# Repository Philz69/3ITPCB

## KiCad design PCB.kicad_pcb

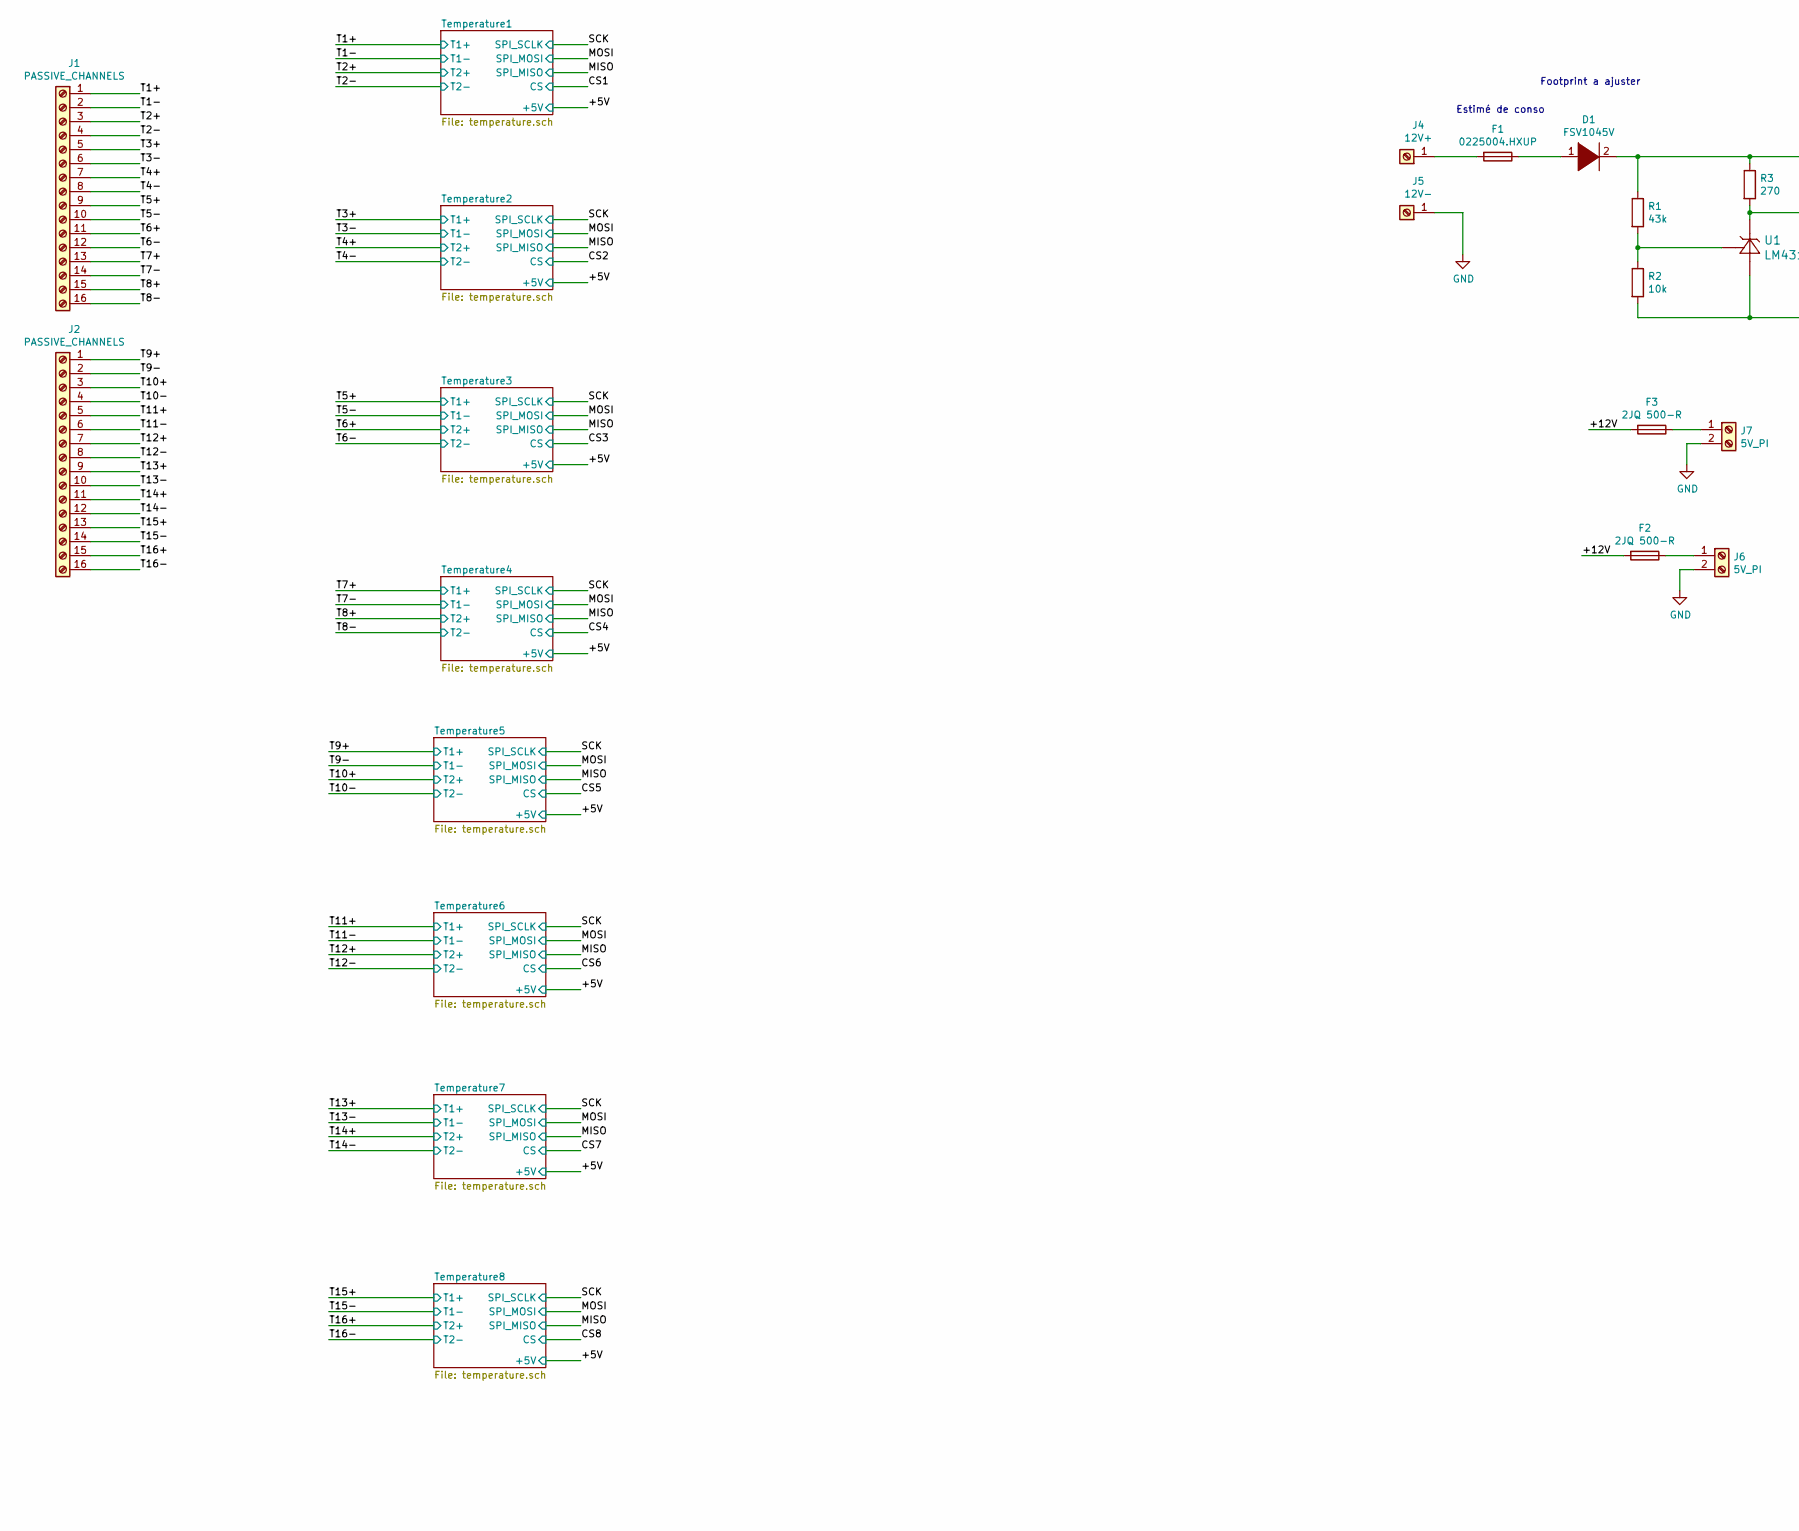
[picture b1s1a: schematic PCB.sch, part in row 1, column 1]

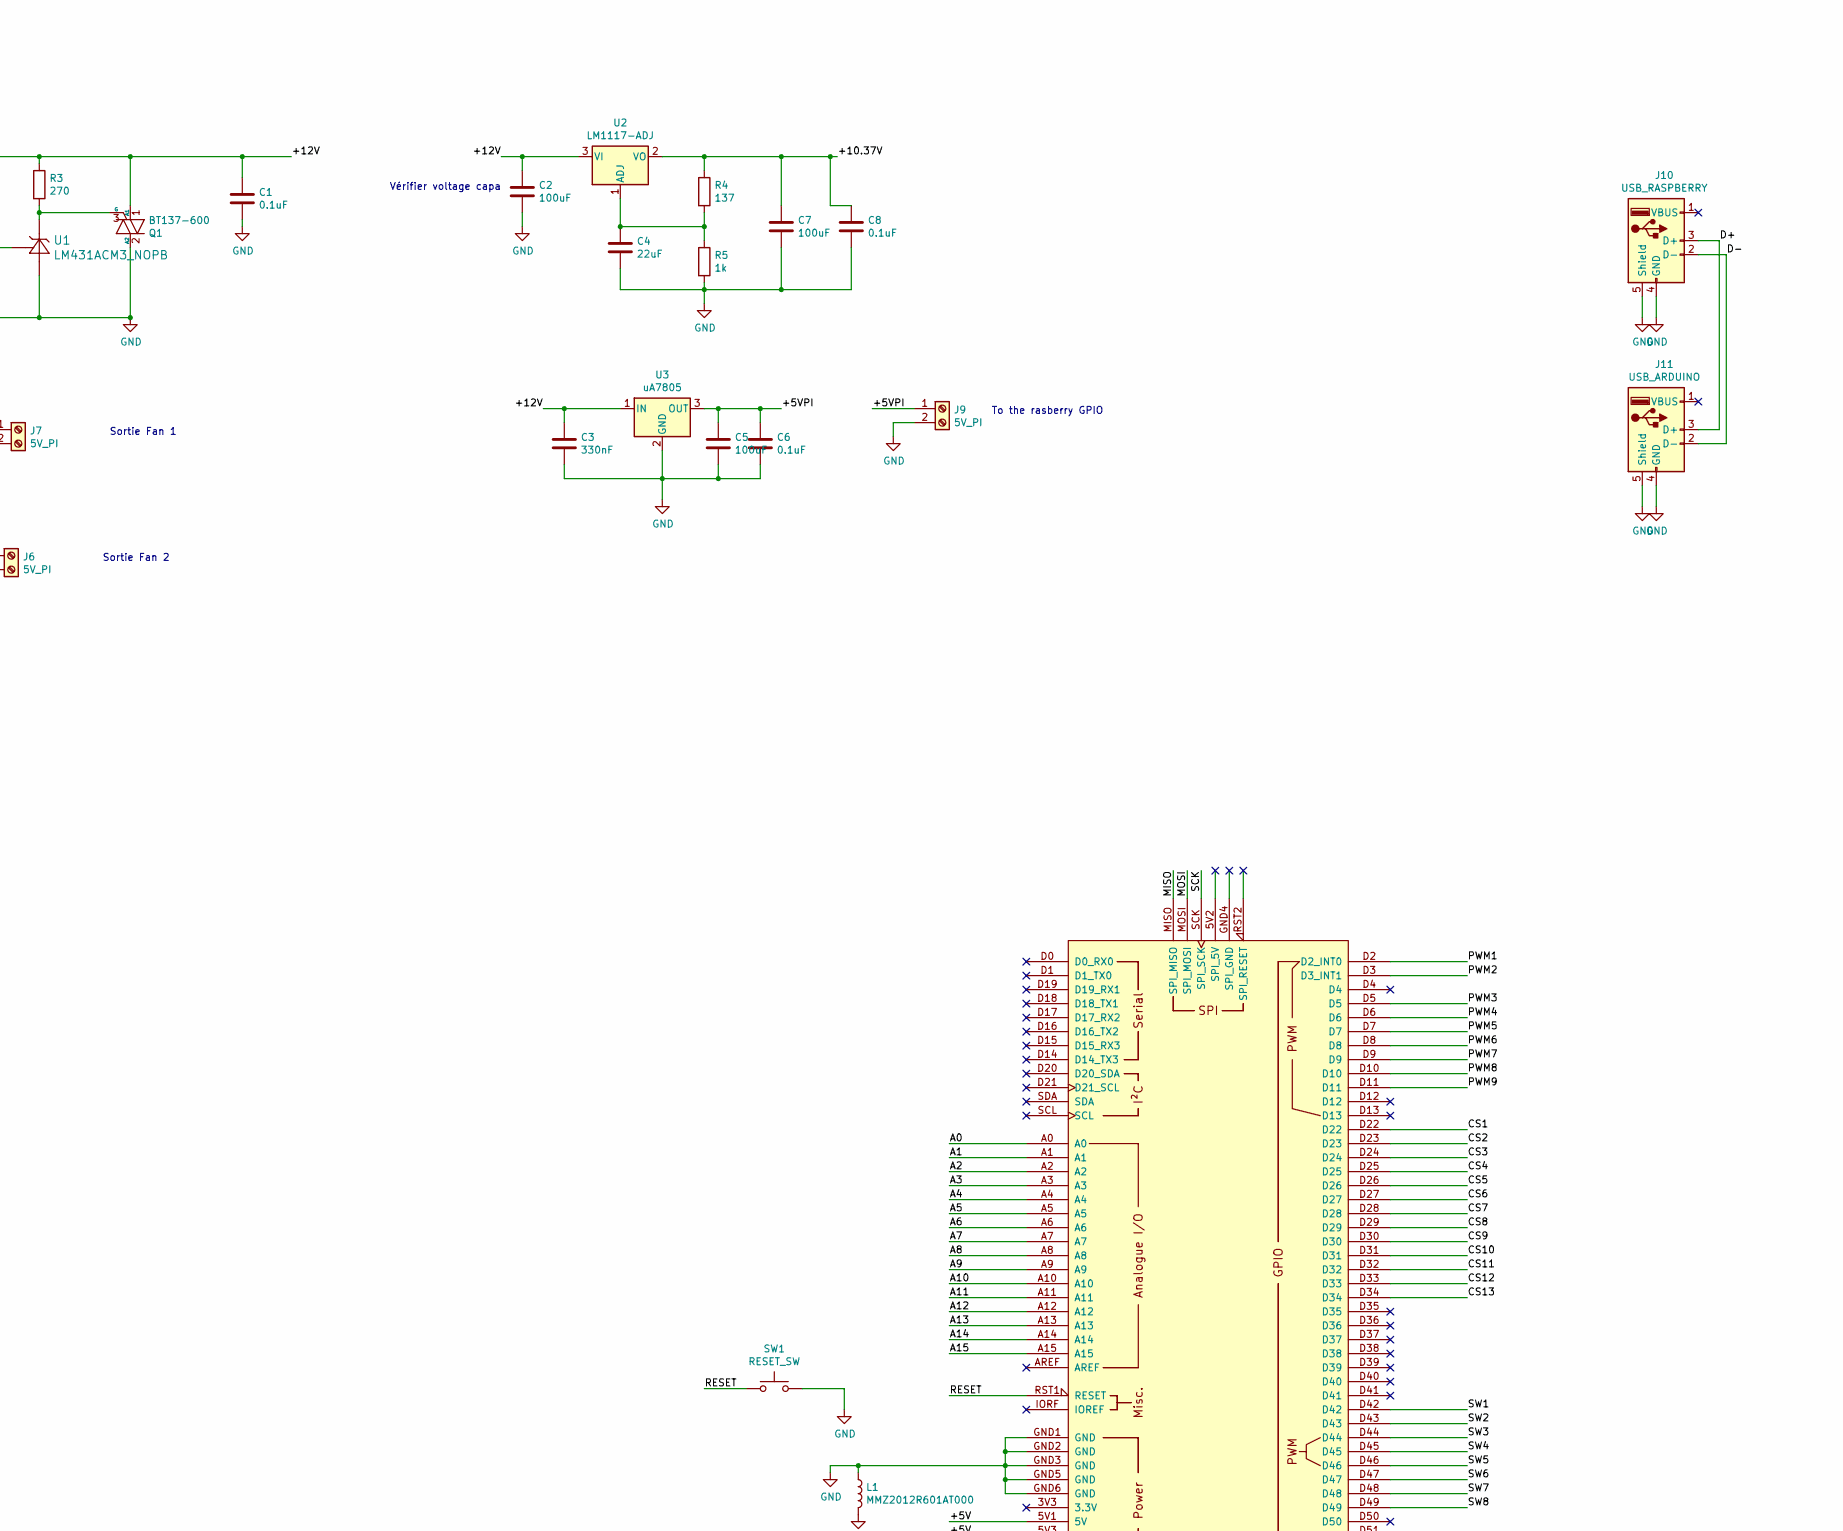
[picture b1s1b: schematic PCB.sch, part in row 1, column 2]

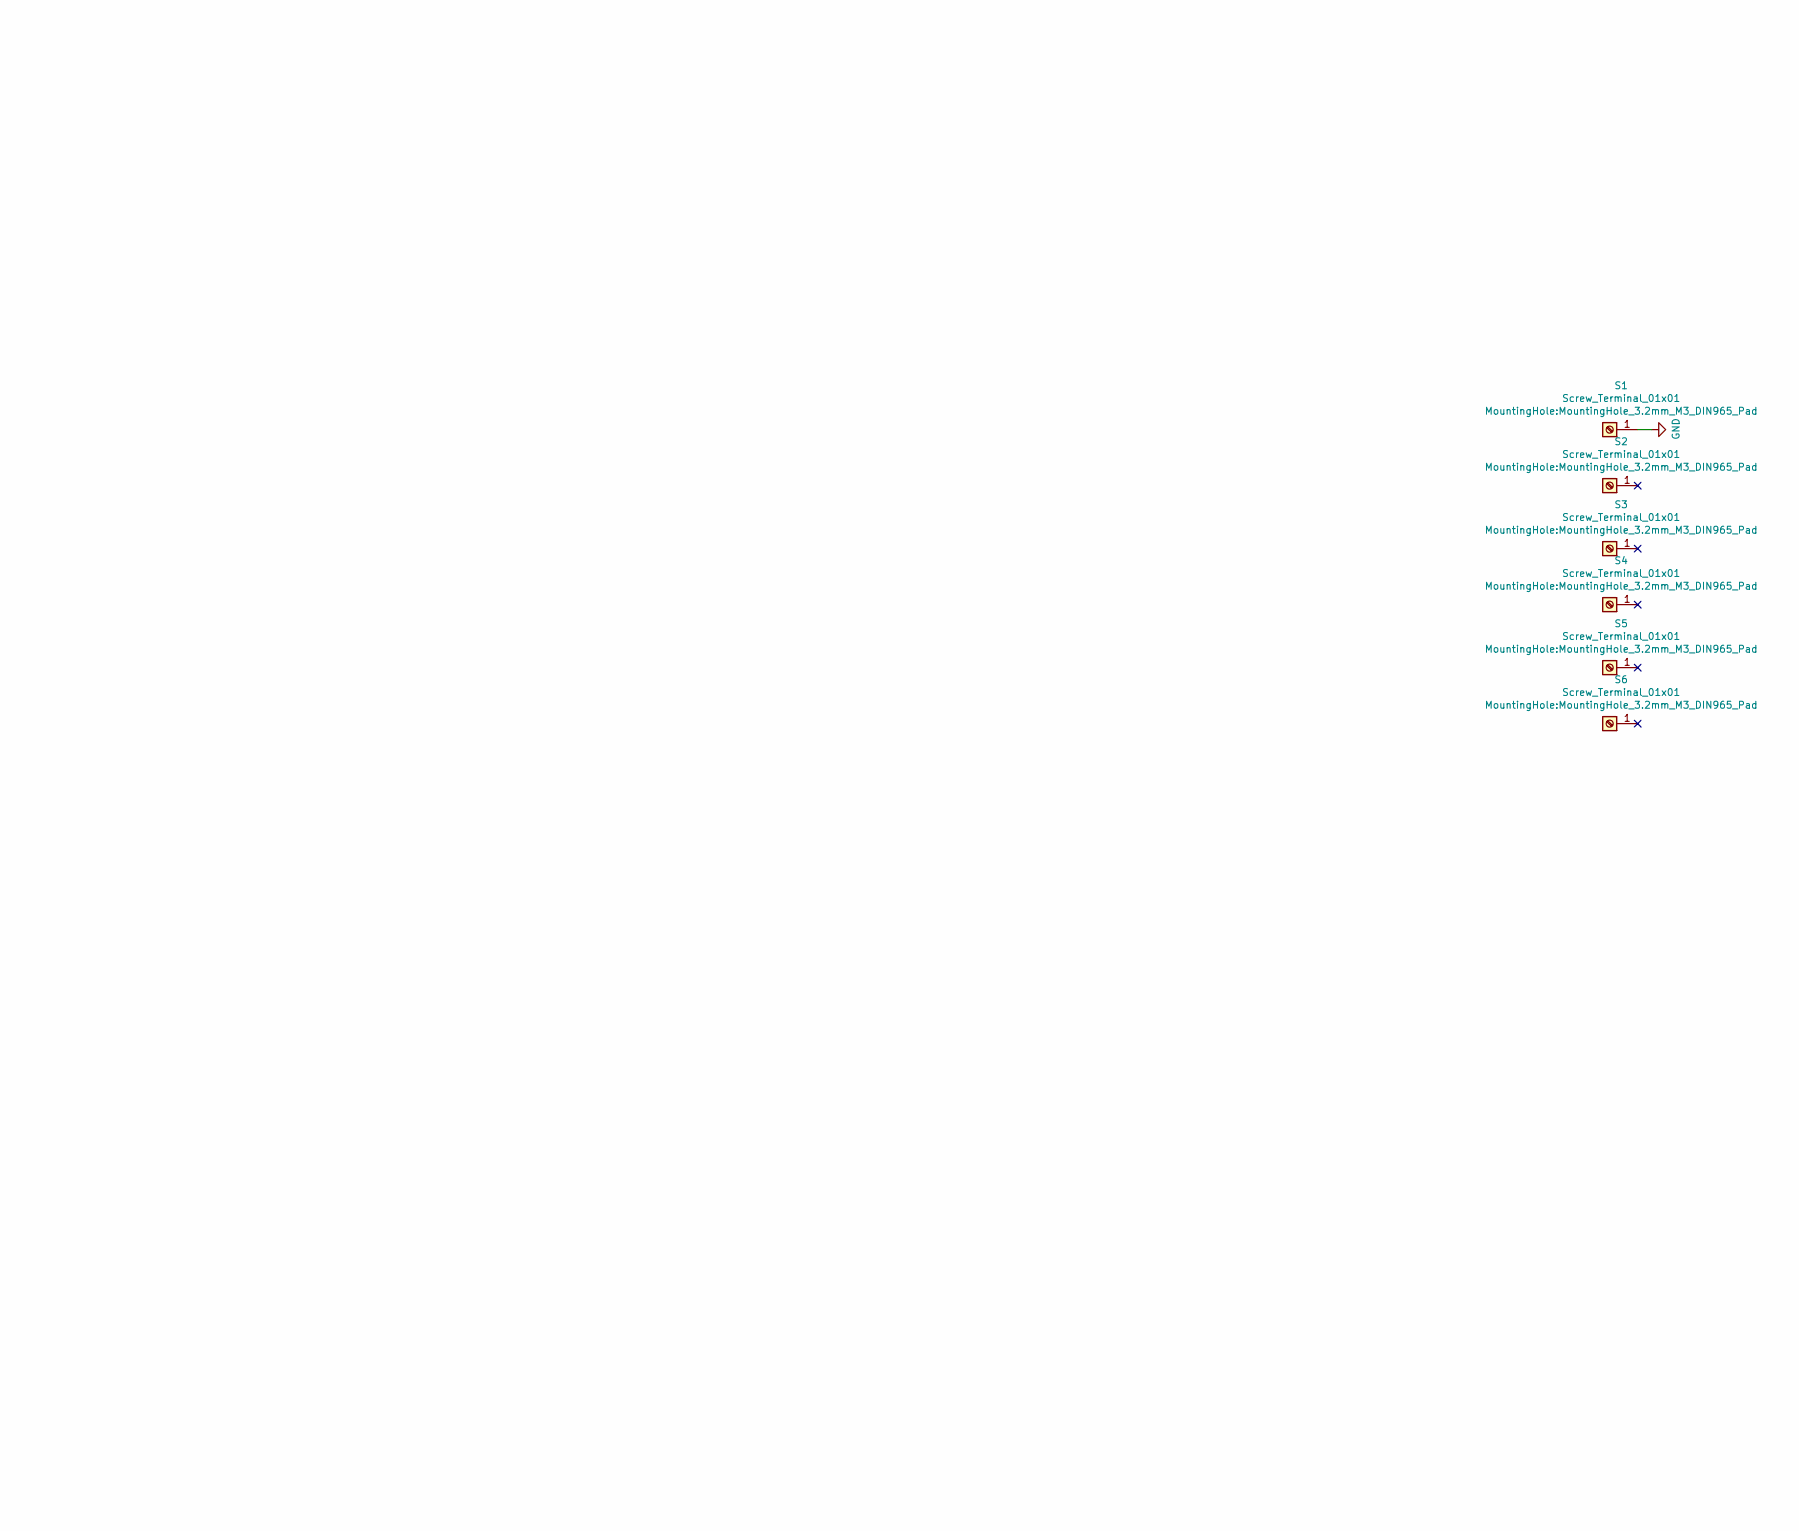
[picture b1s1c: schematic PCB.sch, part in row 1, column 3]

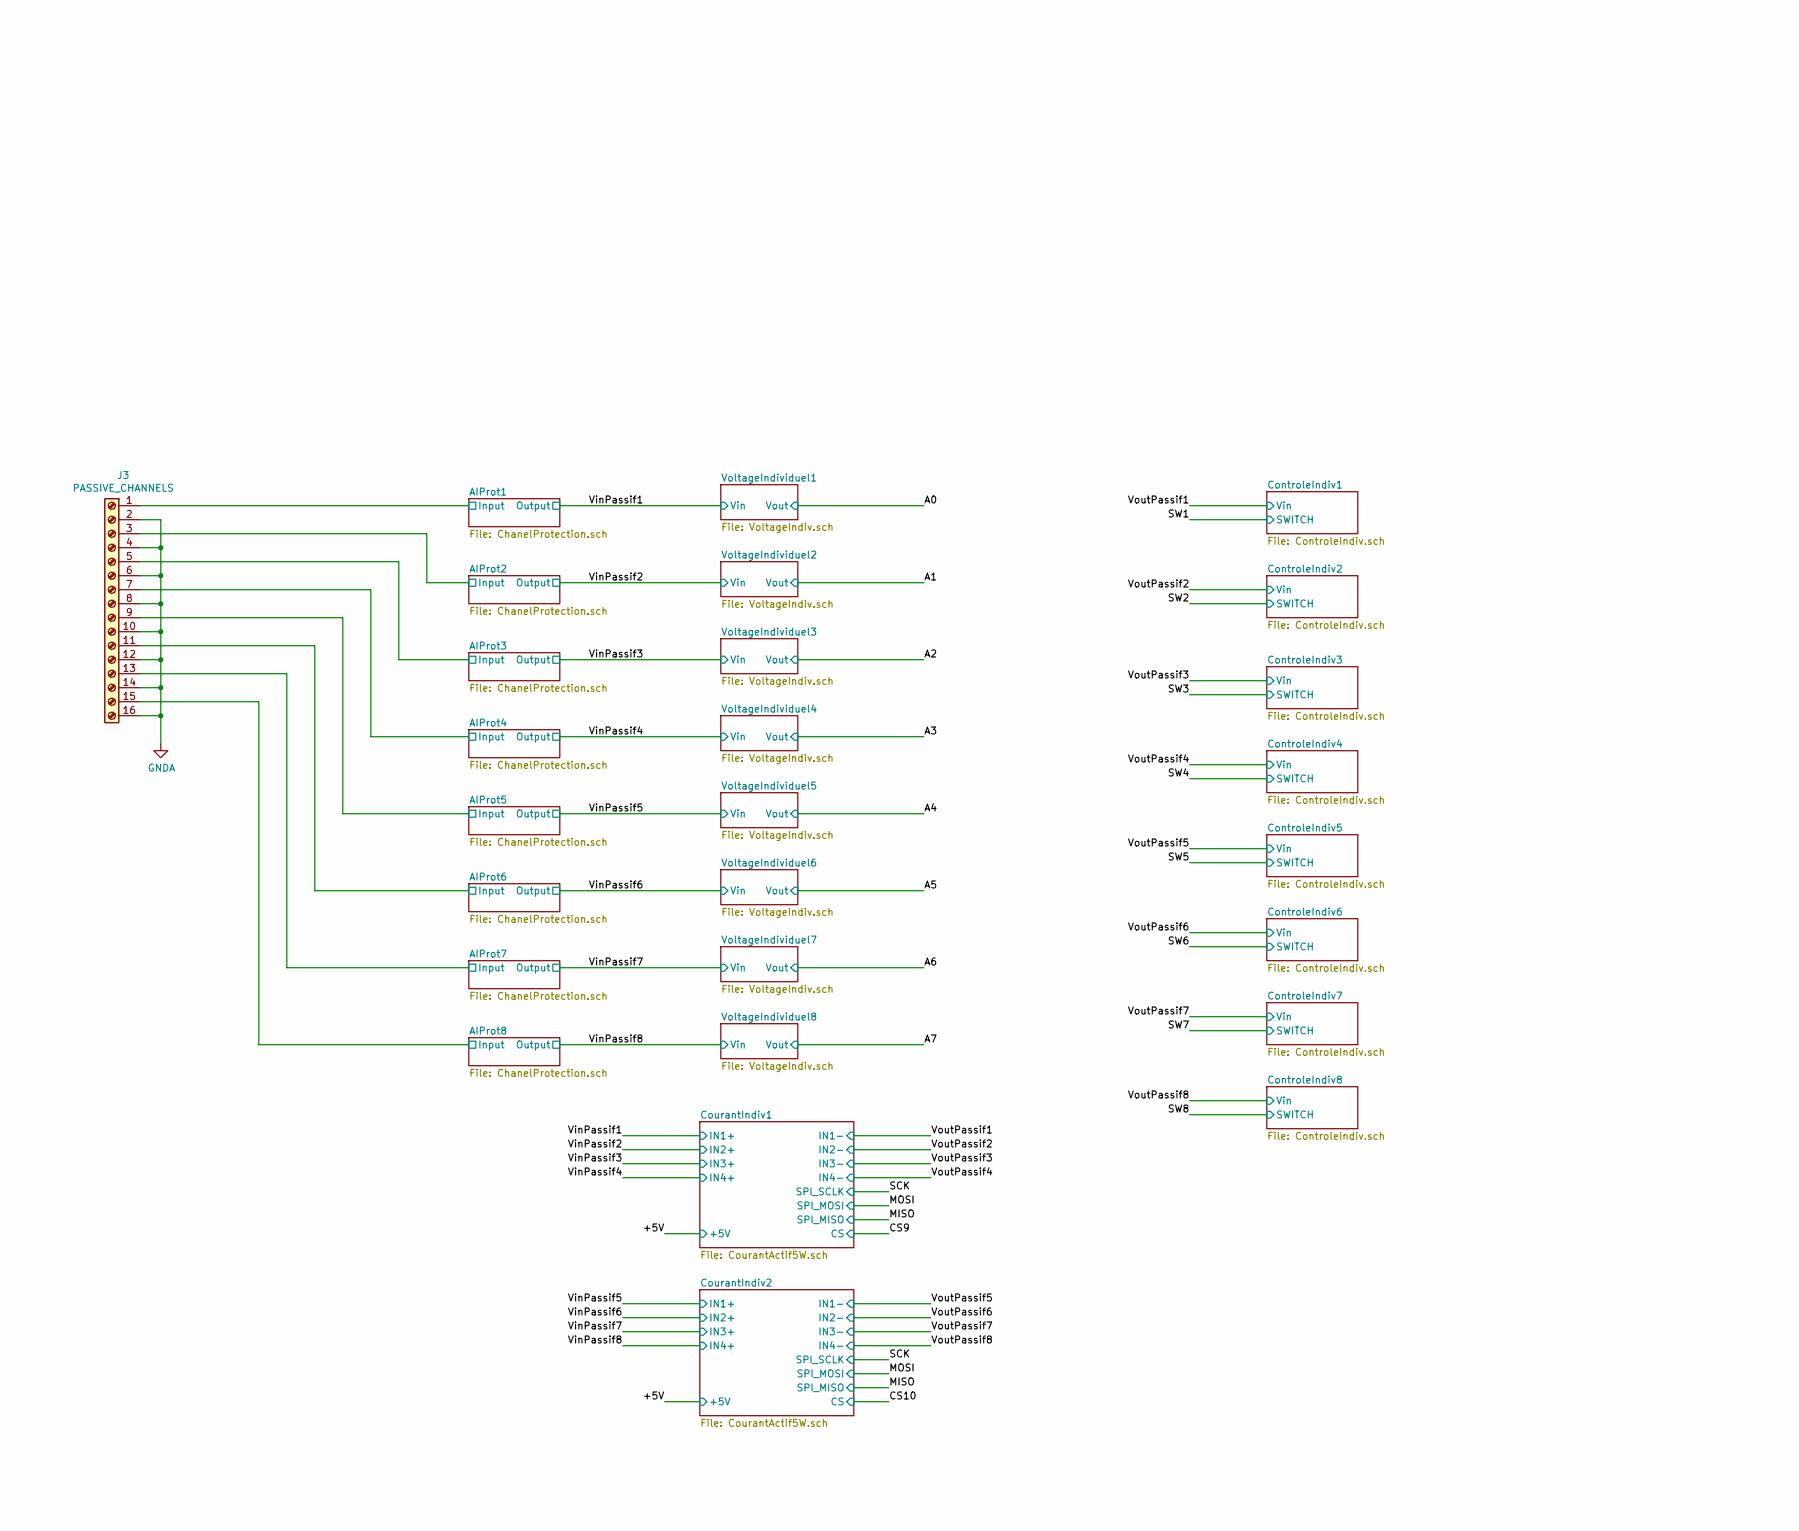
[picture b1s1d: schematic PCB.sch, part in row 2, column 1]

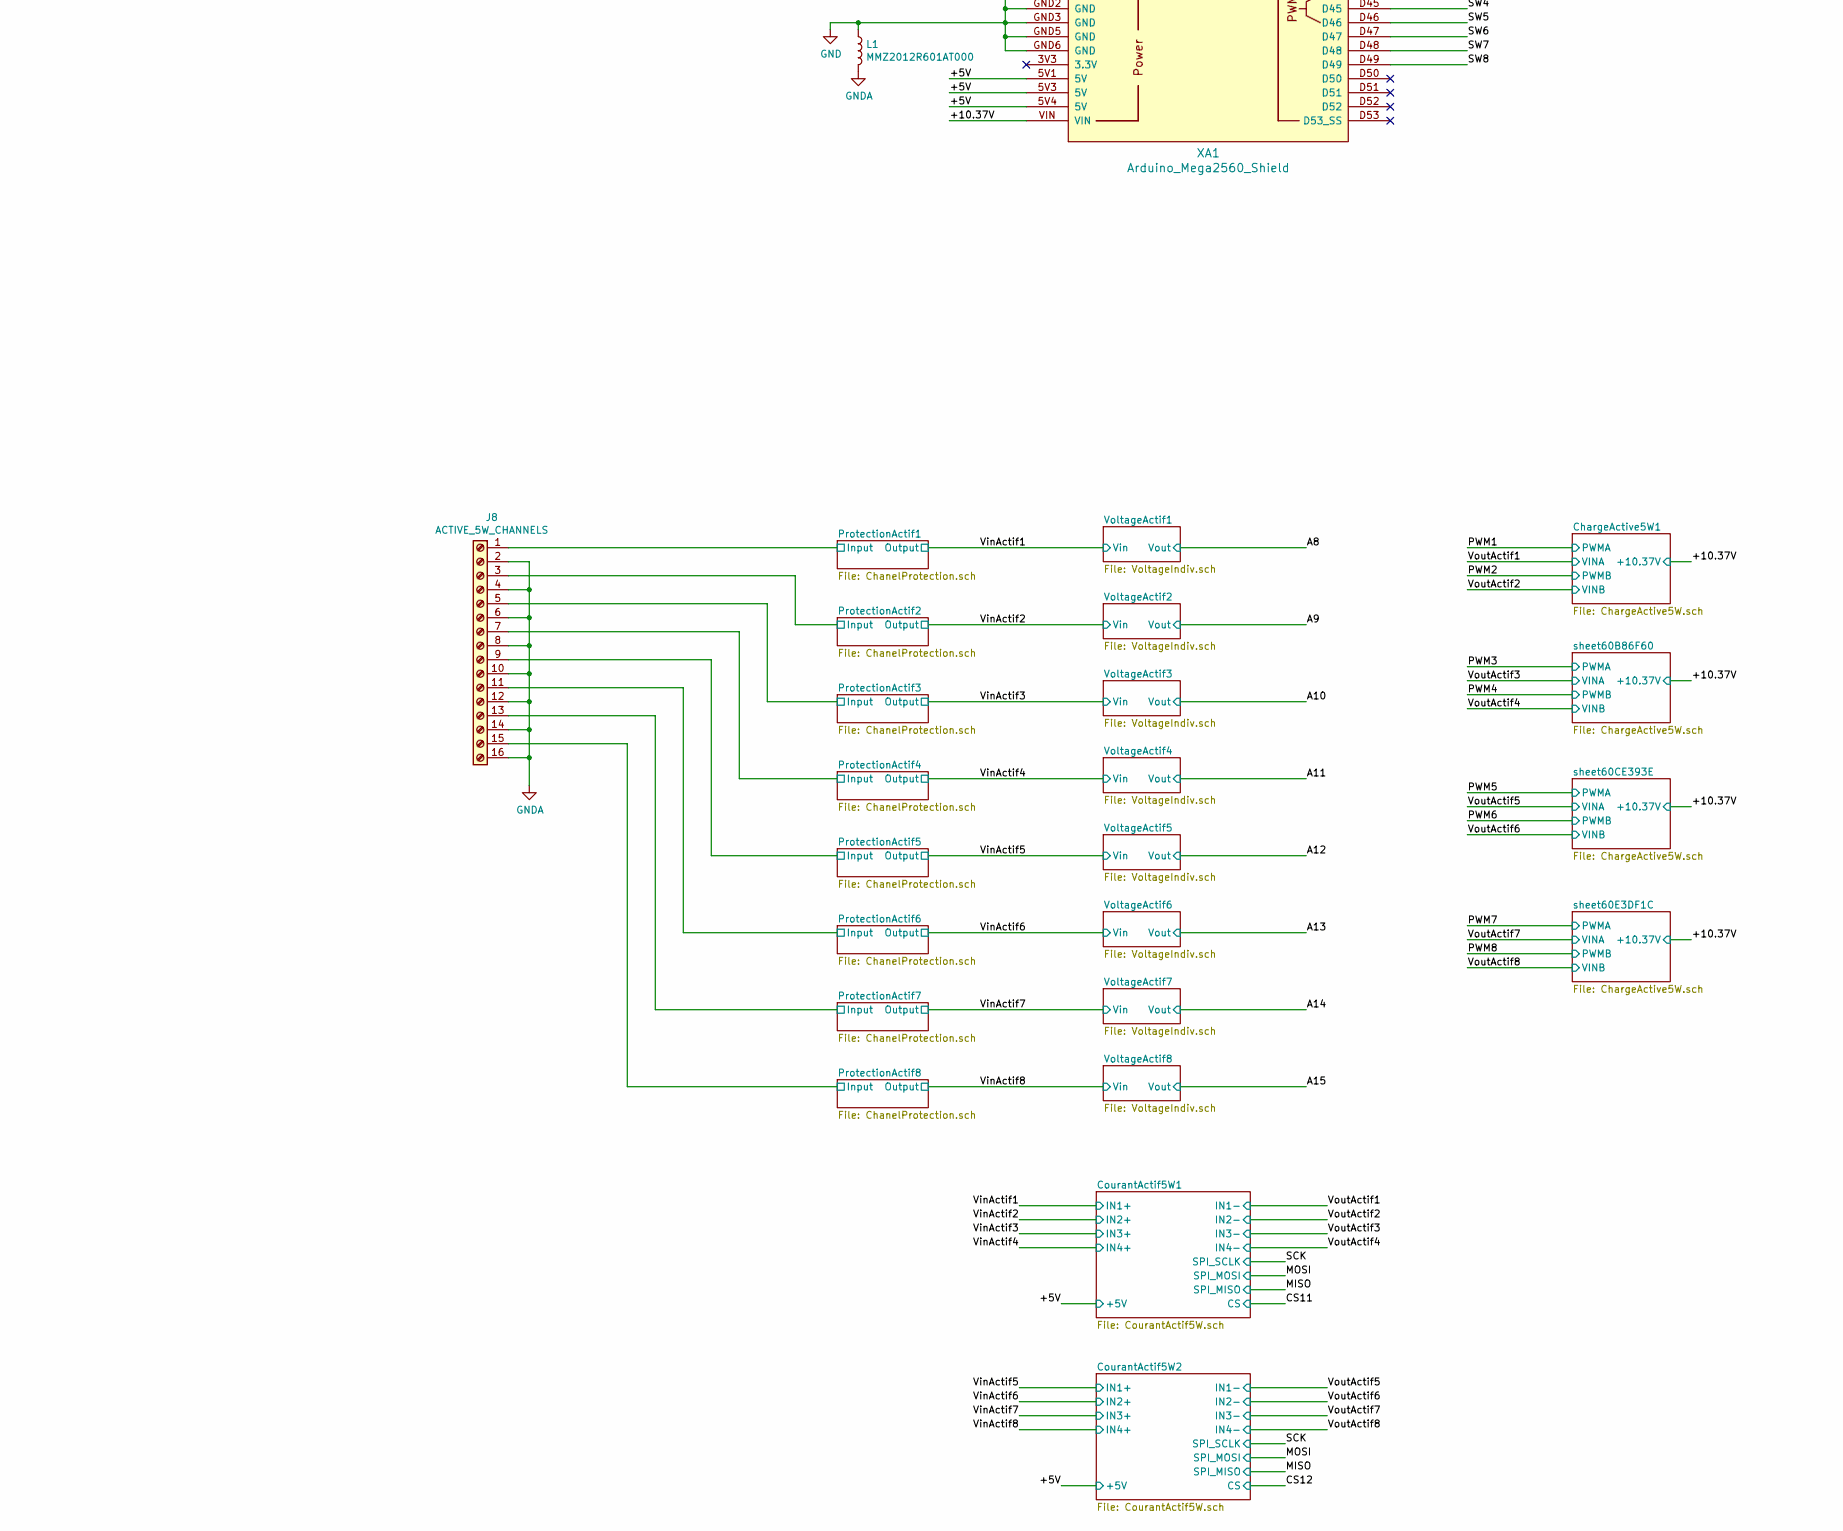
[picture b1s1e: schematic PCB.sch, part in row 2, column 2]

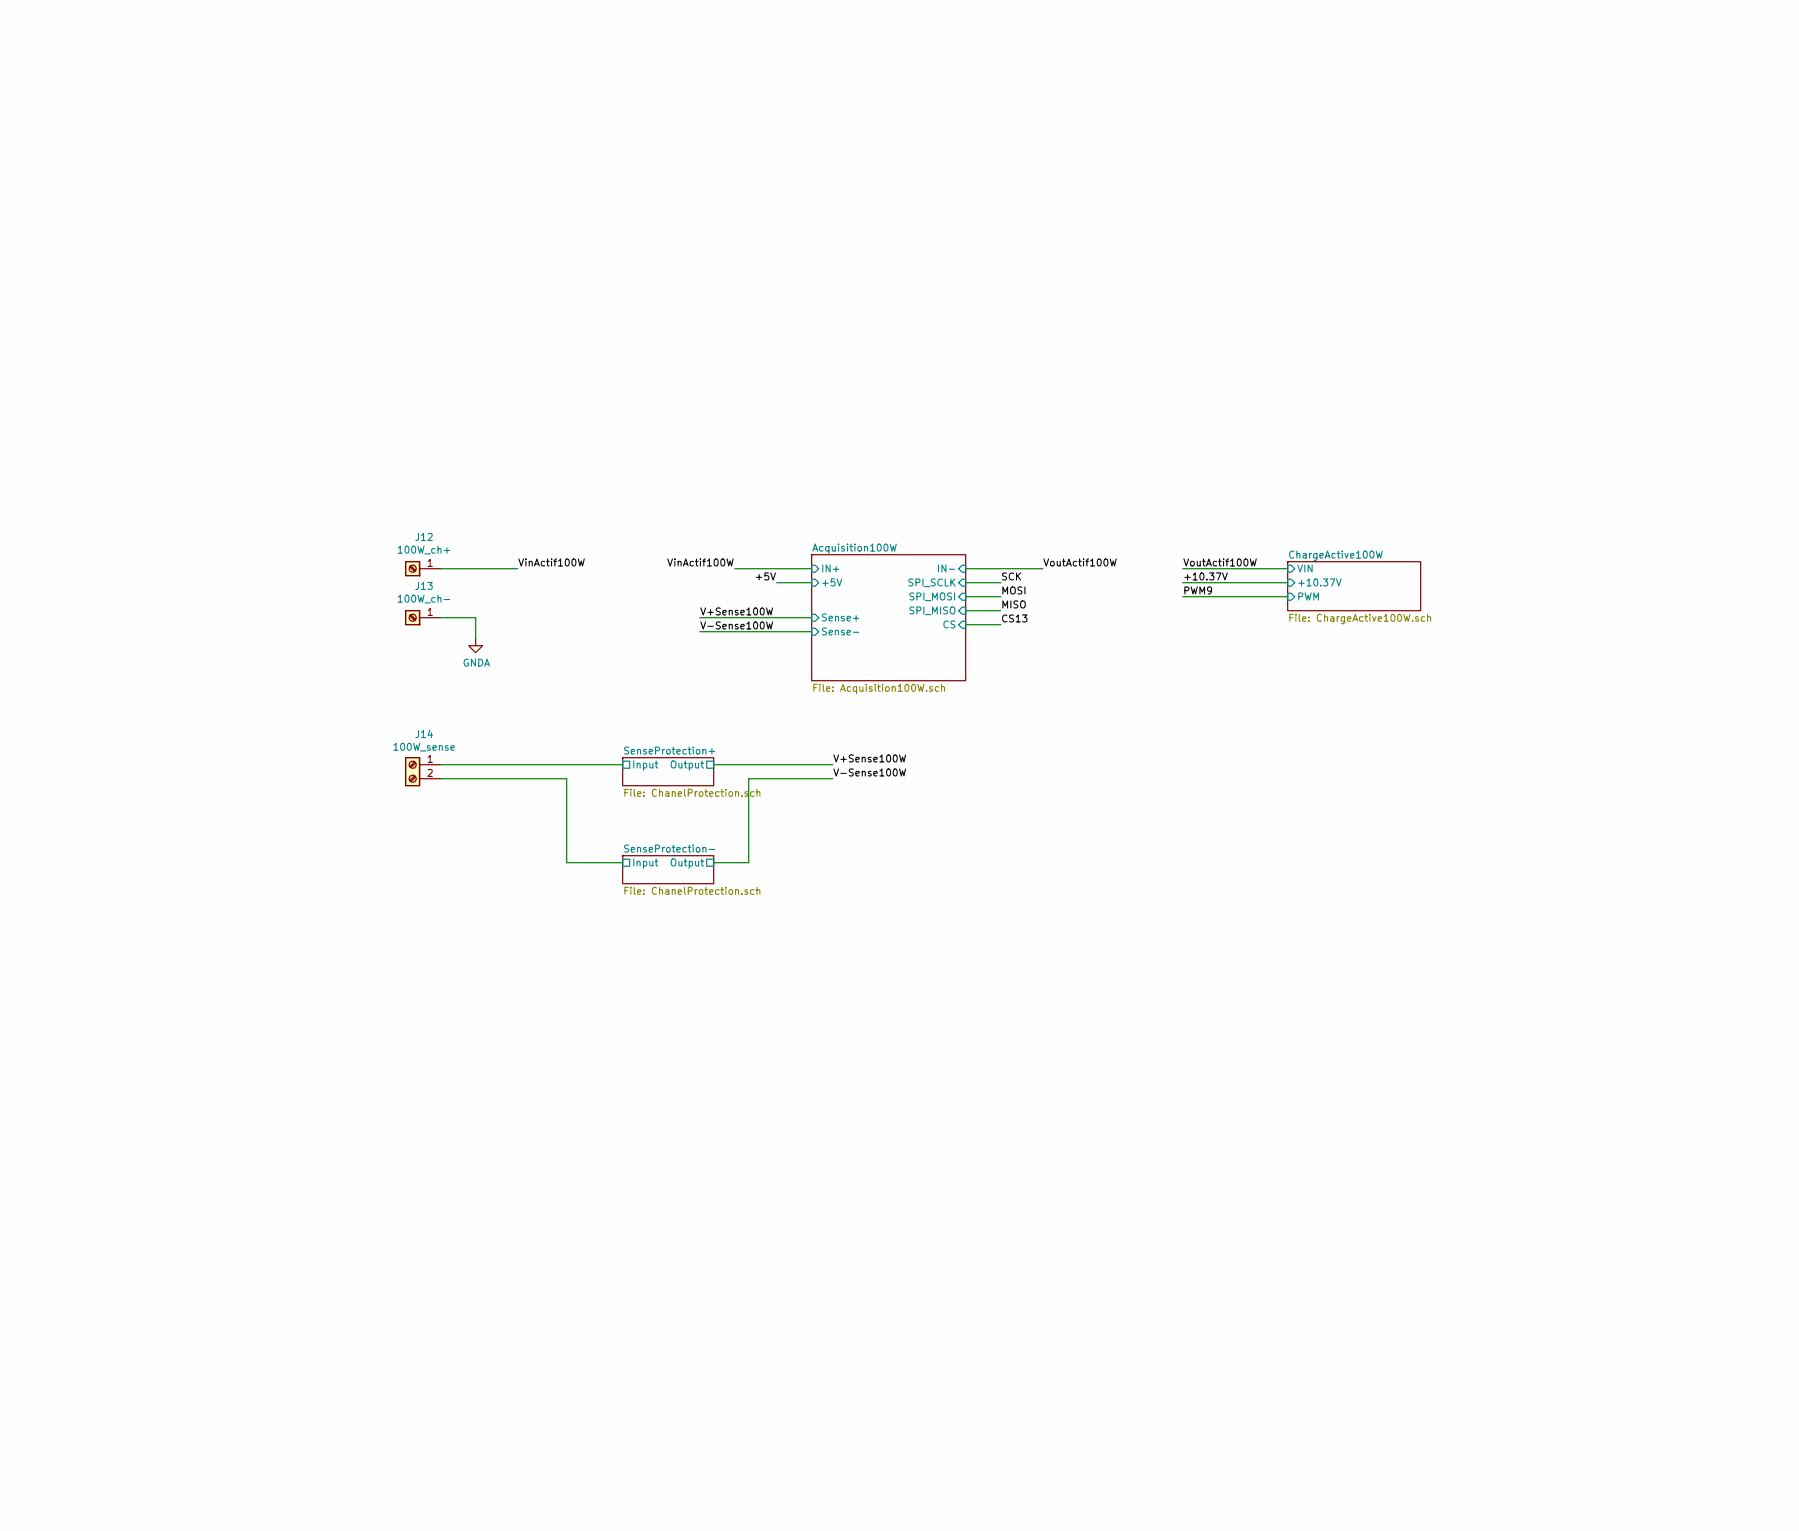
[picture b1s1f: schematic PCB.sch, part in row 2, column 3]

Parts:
C1, C6, C8: 0.1uF; C_0402_1005Metric
C2, C5, C7: 100uF; C_1210_3225Metric
C3: 330nF; C_0603_1608Metric
C4: 22uF; C_0805_2012Metric
D1: FSV1045V; TO-277A
F1: 0225004.HXUP; Fuse5x15mm
F2, F3: 2JQ 500-R; Fuse5x15mm
J1, J2, J3: PASSIVE_CHANNELS; TerminalBlock_Phoenix_PT-1,5-16-5.0-H_1x16_P5.00mm_Horizont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
J4: 12V+; 30ATerminal
J5: 12V-; 30ATerminal
J6, J7, J9: 5V_PI; TerminalBlock_Phoenix_PT-1,5-2-5.0-H_1x02_P5.00mm_Horizontal
J8: ACTIVE_5W_CHANNELS; TerminalBlock_Phoenix_PT-1,5-16-5.0-H_1x16_P5.00mm_Horizont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
J10: USB_RASPBERRY; USB_A_Stewart_SS-52100-001_Horizontal
J11: USB_ARDUINO; USB_A_Stewart_SS-52100-001_Horizontal
J12: 100W_ch+; 30ATerminal
J13: 100W_ch-; 30ATerminal
J14: 100W_sense; TerminalBlock_Phoenix_PT-1,5-2-5.0-H_1x02_P5.00mm_Horizontal
L1: MMZ2012R601AT000; L_0805_2012Metric_Pad1.15x1.40mm_HandSolder
Q1: BT137-600; TO-220-3_Horizontal_TabDown_AccessHole
R1: 43k; R_0603_1608Metric
R2: 10k; R_0603_1608Metric
R3: 270; R_2512_6332Metric
R4: 137; R_1206_3216Metric
R5: 1k; R_1206_3216Metric
S1, S2, S3, S4, S5, S6: Screw_Terminal_01x01; MountingHole_3.2mm_M3_DIN965_Pad
SW1: RESET_SW; SW_SPST_TL3305C
U1: LM431ACM3_NOPB; SOIC-8_3.9x4.9mm_P1.27mm
U2: LM1117-ADJ; TO-220-3_Horizontal_TabDown_AccessHole
U3: uA7805; TO-220-3_Horizontal_TabDown_AccessHole
XA1: Arduino_Mega2560_Shield; Arduino_Mega2560_Socket

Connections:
/+5V: XA1.5V1 (5V), XA1.5V3 (5V), XA1.5V4 (5V); also elsewhere on the board
/+5VPI: C5.1, C6.1, J9.1, U3.3 (OUT)
/+10.37V: C7.1, C8.1, R4.1, U2.2 (VO), XA1.VIN; also elsewhere on the board
/+12V: C1.1, C2.1, C3.1, D1.2 (A), F2.2, F3.2, Q1.1 (A1), R1.1, R3.1, U2.3 (VI), U3.1 (IN)
/A0: XA1.A0; also elsewhere on the board
/A1: XA1.A1; also elsewhere on the board
/A2: XA1.A2; also elsewhere on the board
/A3: XA1.A3; also elsewhere on the board
/A4: XA1.A4; also elsewhere on the board
/A5: XA1.A5; also elsewhere on the board
/A6: XA1.A6; also elsewhere on the board
/A7: XA1.A7; also elsewhere on the board
/A8: XA1.A8; also elsewhere on the board
/A9: XA1.A9; also elsewhere on the board
/A10: XA1.A10; also elsewhere on the board
/A11: XA1.A11; also elsewhere on the board
/A12: XA1.A12; also elsewhere on the board
/A13: XA1.A13; also elsewhere on the board
/A14: XA1.A14; also elsewhere on the board
/A15: XA1.A15; also elsewhere on the board
/AIProt1/Input: J3.1; also elsewhere on the board
/AIProt2/Input: J3.3; also elsewhere on the board
/AIProt3/Input: J3.5; also elsewhere on the board
/AIProt4/Input: J3.7; also elsewhere on the board
/AIProt5/Input: J3.9; also elsewhere on the board
/AIProt6/Input: J3.11; also elsewhere on the board
/AIProt7/Input: J3.13; also elsewhere on the board
/AIProt8/Input: J3.15; also elsewhere on the board
/CS1: XA1.D22; also elsewhere on the board
/CS2: XA1.D23; also elsewhere on the board
/CS3: XA1.D24; also elsewhere on the board
/CS4: XA1.D25; also elsewhere on the board
/CS5: XA1.D26; also elsewhere on the board
/CS6: XA1.D27; also elsewhere on the board
/CS7: XA1.D28; also elsewhere on the board
/CS8: XA1.D29; also elsewhere on the board
/CS9: XA1.D30; also elsewhere on the board
/CS10: XA1.D31; also elsewhere on the board
/CS11: XA1.D32; also elsewhere on the board
/CS12: XA1.D33; also elsewhere on the board
/CS13: XA1.D34; also elsewhere on the board
/D+: J10.3 (D+), J11.3 (D+)
/D-: J10.2 (D-), J11.2 (D-)
/MISO: XA1.MISO (SPI_MISO); also elsewhere on the board
/MOSI: XA1.MOSI (SPI_MOSI); also elsewhere on the board
/PWM1: XA1.D2 (D2_INT0); also elsewhere on the board
/PWM2: XA1.D3 (D3_INT1); also elsewhere on the board
/PWM3: XA1.D5; also elsewhere on the board
/PWM4: XA1.D6; also elsewhere on the board
/PWM5: XA1.D7; also elsewhere on the board
/PWM6: XA1.D8; also elsewhere on the board
/PWM7: XA1.D9; also elsewhere on the board
/PWM8: XA1.D10; also elsewhere on the board
/PWM9: XA1.D11; also elsewhere on the board
/ProtectionActif1/Input: J8.1; also elsewhere on the board
/ProtectionActif2/Input: J8.3; also elsewhere on the board
/ProtectionActif3/Input: J8.5; also elsewhere on the board
/ProtectionActif4/Input: J8.7; also elsewhere on the board
/ProtectionActif5/Input: J8.9; also elsewhere on the board
/ProtectionActif6/Input: J8.11; also elsewhere on the board
/ProtectionActif7/Input: J8.13; also elsewhere on the board
/ProtectionActif8/Input: J8.15; also elsewhere on the board
/RESET: SW1.1, XA1.RST1 (RESET)
/SCK: XA1.SCK (SPI_SCK); also elsewhere on the board
/SW1: XA1.D42; also elsewhere on the board
/SW2: XA1.D43; also elsewhere on the board
/SW3: XA1.D44; also elsewhere on the board
/SW4: XA1.D45; also elsewhere on the board
/SW5: XA1.D46; also elsewhere on the board
/SW6: XA1.D47; also elsewhere on the board
/SW7: XA1.D48; also elsewhere on the board
/SW8: XA1.D49; also elsewhere on the board
/SenseProtection+/Input: J14.1; also elsewhere on the board
/SenseProtection-/Input: J14.2; also elsewhere on the board
/T1+: J1.1; also elsewhere on the board
/T1-: J1.2; also elsewhere on the board
/T2+: J1.3; also elsewhere on the board
/T2-: J1.4; also elsewhere on the board
/T3+: J1.5; also elsewhere on the board
/T3-: J1.6; also elsewhere on the board
/T4+: J1.7; also elsewhere on the board
/T4-: J1.8; also elsewhere on the board
/T5+: J1.9; also elsewhere on the board
/T5-: J1.10; also elsewhere on the board
/T6+: J1.11; also elsewhere on the board
/T6-: J1.12; also elsewhere on the board
/T7+: J1.13; also elsewhere on the board
/T7-: J1.14; also elsewhere on the board
/T8+: J1.15; also elsewhere on the board
/T8-: J1.16; also elsewhere on the board
/T9+: J2.1; also elsewhere on the board
/T9-: J2.2; also elsewhere on the board
/T10+: J2.3; also elsewhere on the board
/T10-: J2.4; also elsewhere on the board
/T11+: J2.5; also elsewhere on the board
/T11-: J2.6; also elsewhere on the board
/T12+: J2.7; also elsewhere on the board
/T12-: J2.8; also elsewhere on the board
/T13+: J2.9; also elsewhere on the board
/T13-: J2.10; also elsewhere on the board
/T14+: J2.11; also elsewhere on the board
/T14-: J2.12; also elsewhere on the board
/T15+: J2.13; also elsewhere on the board
/T15-: J2.14; also elsewhere on the board
/T16+: J2.15; also elsewhere on the board
/T16-: J2.16; also elsewhere on the board
/VinActif100W: J12.1; also elsewhere on the board
GND: C1.2, C2.2, C3.2, C4.2, C5.2, C6.2, C7.2, C8.2, J5.1, J6.2, J7.2, J9.2, J10.4 (GND), J10.5 (Shield), J11.4 (GND), J11.5 (Shield), L1.1, Q1.2 (A2), R2.2, R5.2, S1.1, SW1.2, U1.3 (A), U3.2 (GND), XA1.GND1 (GND), XA1.GND2 (GND), XA1.GND3 (GND), XA1.GND5 (GND), XA1.GND6 (GND); also elsewhere on the board
GNDA: J3.2, J3.4, J3.6, J3.8, J3.10, J3.12, J3.14, J3.16, J8.2, J8.4, J8.6, J8.8, J8.10, J8.12, J8.14, J8.16, J13.1, L1.2; also elsewhere on the board
unnamed: C4.1, R4.2, R5.1, U2.1 (ADJ)
unnamed: D1.1 (K), F1.1
unnamed: F1.2, J4.1
unnamed: F2.1, J6.1
unnamed: F3.1, J7.1
unnamed: Q1.3 (G), R3.2, U1.1 (K)
unnamed: R1.2, R2.1, U1.2 (REF)

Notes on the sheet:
Sortie Fan 1
Sortie Fan 2
Footprint a ajuster
Estimé de conso
Vérifier voltage capa
To the rasberry GPIO

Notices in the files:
PCB.kicad_pcb:
This work is licensed under the
Creative Commons Attribution-ShareAlike 4.0 International License.
http://creativecommons.org/licenses/by-sa/4.0
Creative Commons,
PO Box 1866,
